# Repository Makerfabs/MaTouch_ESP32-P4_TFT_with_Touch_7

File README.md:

If you encounter the following error when compiling under Windows, please try enabling Windows long path support.
```txt
\MaTouch_ESP32-P4_TFT_with_Touch_7\examples\esp_brookesia_phone\managed_components\espressif__esp_wifi_remote\dummy_src.c.obj.d: No such file or directory
```

do :

```cmd
# Open PowerShell with administrator privileges
reg add "HKLM\SYSTEM\CurrentControlSet\Control\FileSystem" /v LongPathsEnabled /t REG_DWORD /d 1
```

Restart the system.

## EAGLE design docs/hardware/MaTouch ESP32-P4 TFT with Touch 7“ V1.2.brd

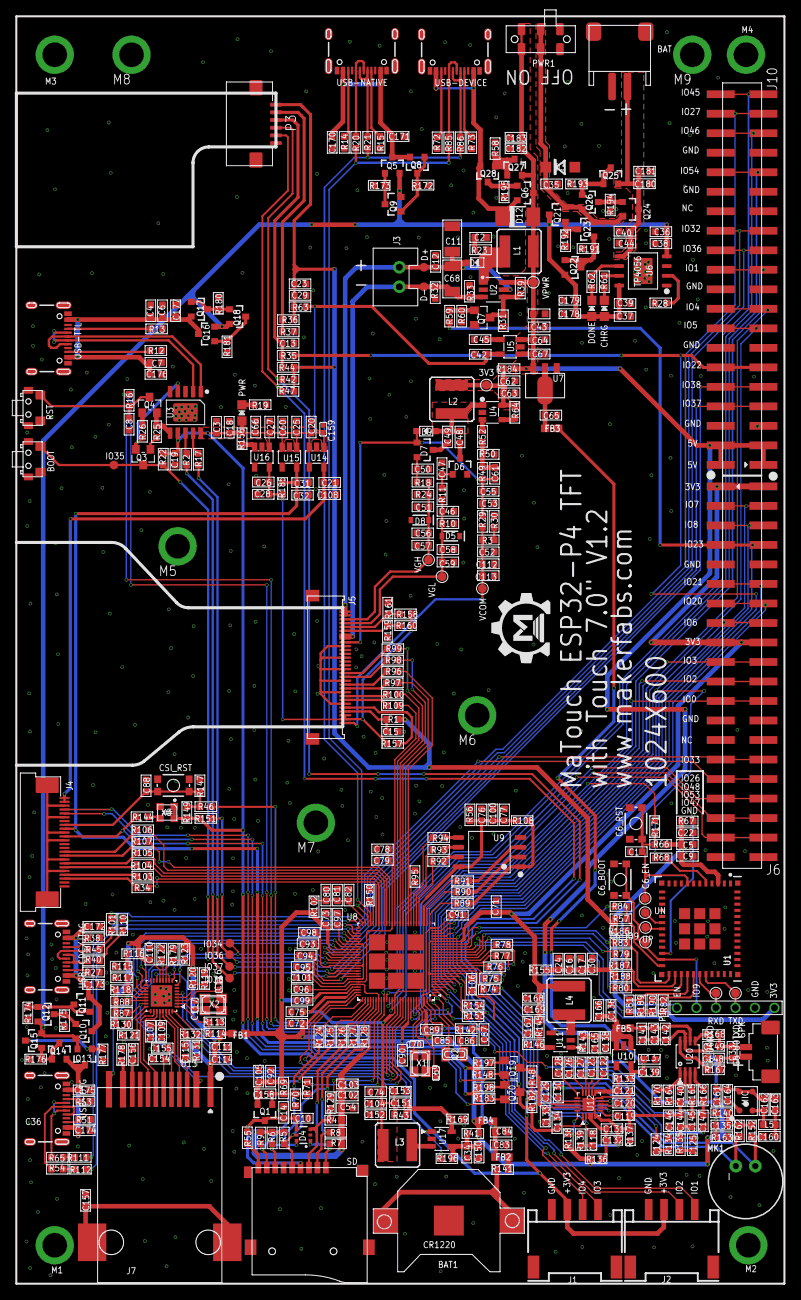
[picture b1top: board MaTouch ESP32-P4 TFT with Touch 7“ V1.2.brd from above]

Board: 2 copper layers, 100.0 x 165.0 mm, 507 parts (0 on the bottom side), 301 nets.

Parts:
3V3: TP_4545
BAT: JST-2P; HW2-SMD-2.0-90D
BAT1: CR1220-SMD
BOOT: TS24CA; 2*4*3.5MM
C1, C93, C94, C95, C96, C121, C124, C125, C126, C127, C128, C129, C130, C135, C140, C141: 1uF/16V; C0603
C2: 10pF/50V; DISCRETE_C0603
C3, C4, C6, C10, C16, C23, C29, C54, C63, C113: 10uF; DISCRETE_C0603
C5, C21, C22, C28, C31, C34, C35, C36, C38, C40, C42, C43, C65, C71, C74, C76, C78, C80, C83, C89, C97, C102, C107, C110, C114, C137, C142, C152, C160, C161, C165, C168, C170, C172, C174, C176, C178, C180, C182: 10uF; C0603
C6_BOOT, C6_RST: MOMENTARY-SWITCH-SPST-SMD-4.6X2.8MM; TACTILE_SWITCH_SMD_4.6X2.8MM
C6_EN, C6_IO9, C6_U0RXD, C6_U0TXD: TP_4545
C7, C8, C14, C17, C18, C19, C24, C26, C30, C32, C46, C47, C48, C49, C50, C51, C52, C53, C55, C60, C62, C66, C108, C112, C158: 0.1uF; DISCRETE_C0603
C9, C37, C39, C44, C67, C72, C73, C75, C77, C79, C81, C84, C90, C91, C92, C98, C99, C100, C103, C104, C105, C106, C109, C111, C115, C131, C132, C138, C139, C143, C145, C147, C150, C153, C154, C155, C166, C169, C171, C173, C175, C177, C179, C181, C183: 0.1uF; C0603
C11: 4.7uF/35V; DISCRETE_C1206
C12: 0.1uF/50V; DISCRETE_C0603
C13: NC; DISCRETE_C0603
C15: 100nF; DISCRETE_C0603
C20, C25, C27, C41, C64, C136: 4.7uF/16V; C0603
C33, C148, C149: 330pF/50V; C0603
C45: NC; C0603
C56, C57, C58, C59: 1uF; DISCRETE_C0603
C61: 10pF/25V; DISCRETE_C0603
C68: NC; DISCRETE_C1206
C69, C70, C116, C117: 12pF; DISCRETE_C0402
C82: 10nF; C0603
C85, C86: 20pF; DISCRETE_C0603
C87, C88: 15pF; DISCRETE_C0603
C101: 1uF; C0603
C118, C119, C120, C122, C123, C133, C134, C144, C146, C151, C167: 22pF; C0603
C156, C157: 1nF/50V; C0603
C159: 100nF; C0402
C162, C163: 33pF; C0603
C164: 100nF; C0603
CHRG: CHRG; CHIPLED_0805_NOOUTLINE
CSI_RST: MOMENTARY-SWITCH-SPST-SMD-4.6X2.8MM; TACTILE_SWITCH_SMD_4.6X2.8MM
D1, D9: 1N4148WS; SOD323
D3: W8/5.1V; SOD123
D4: SMF05C; SOT363
D5: 7.5V; SOD-323
D6, D7: 200mA/70V; SOT23-3
D8: 20V; SOD-323
D12: SS54; DO-214AC
D+: TP-D45MIL
D-: TP-D45MIL
DONE: GREEN; CHIPLED_0805_NOOUTLINE
FB1, FB2, FB3, FB4, FB5: 0603
IO34, IO35, IO36, IO37, IO38: TP-D45MIL
J1, J2: HW4-SMD-2.0-90D
J3: XH2.54-2P
J4: SMD26-50P-1760L450W
J5: 30P-0.5-90D-18.4X5.0
J6, J10: SMD2X20-254P-5080L750W920H
J7: HR961160C
L1, L2: 10µH/±30%; CR54
L3, L4: 2.2µH/±30%/3.4A; CR54
L5: BLM18BD252SN1; L0603
M1, M2, M3, M4, M5, M6, M7, M8, M9: M2.5
MIC: SAO-3729-M-42-008; MIC4-SMD-3.76X2.95MM
MK1: MIC-PTH; MICROPHONE-PTH-9.7MM
P1: DEBUG6; DEBUG*6
P3: 1X6P-1MM; 1*6P-SMT1MM
PWR: GREEN; CHIPLED_0805_NOOUTLINE
PWR1: JS102011JAQN; SMD-6-2.5MM
Q1, Q5, Q6, Q10, Q13, Q16, Q21, Q24: MOSFET-PCHANNEL; SOT23-3
Q2: 32.768K; XTAL3215
Q3, Q4, Q7: S8050; SOT23
Q8, Q9, Q11, Q12, Q14, Q15, Q17, Q18, Q22, Q23, Q25, Q26, Q27, Q28: 600mA/40V; SOT23-3
Q19, Q20: BS138; SOT23
R1, R39, R44, R58, R60, R64, R69, R70, R108, R156, R157, R158, R159, R172, R174, R176, R180, R191, R193: 10K; DISCRETE_R0603
R2, R17, R35, R41, R56, R63, R68, R74, R75, R76, R77, R78, R79, R80, R81, R82, R83, R84, R89, R90, R91, R92, R93, R94, R96, R97, R98, R99, R100, R102, R109, R124, R125, R126, R127, R128, R129, R133, R134, R135, R136, R137, R144, R147, R153, R154, R155, R163, R167, R168, R170, R171, R184, R185: 0R; R0603
R3: 0R; DISCRETE_R0603
R4, R6, R7, R8, R9, R10, R24, R55, R57, R173, R175, R177, R181, R186, R187, R188, R189, R190, R192, R194, R195: 51K; DISCRETE_R0603
R5, R31, R36, R37, R42, R47, R149, R160, R161: NC; DISCRETE_R0603
R11, R18: 220R; DISCRETE_R0603
R12, R13, R14, R15, R27, R38, R51, R53, R72, R73: 5.1K; DISCRETE_R0603
R16, R22, R25, R26, R66, R139, R143, R151, R164: 10K; R0603
R19: 1.2K; DISCRETE_R0603
R20, R21, R40, R45, R54, R65, R71, R85, R86, R101, R110, R111, R112: 33R; R0603
R23: 50R; DISCRETE_R0603
R28, R61, R62: 1.2K; R0603
R29: 2K; DISCRETE_R0603
R30: 1K; DISCRETE_R0603
R32, R33: 3.6R; DISCRETE_R0603
R34, R103, R104, R105, R106, R107: 100R; R0603
R43, R169: 499K/NC; R0603
R46, R196: NC; R0603
R48, R182: 3.3K; R0603
R49: 22K; DISCRETE_R0603
R50: 3.3K; DISCRETE_R0603
R52: 0K; DISCRETE_R0603
R59: 4.7K; DISCRETE_R0603
R67, R145: 100K; R0603
R87, R178, R179: 1.5K; R0603
R88: 1.5K/NC; R0603
R95, R150: 4.02K; R0603
R113, R116, R118, R120, R122, R123: 5.1K; R0603
R114, R115, R117, R119, R130: NC/5.1K; R0603
R121: 6.19K; R0603
R131, R132: NC/10K; R0603
R138: 10K/NC; R0603
R140: 200R; R0603
R141: 10R; R0603
R142: 0R/NC; R0603
R146: 22.1K; R0603
R148, R152, R162, R183, R197, R198: 2.2K; R0603
R165, R166: 150K; R0603
RST: TS24CA; 2*4*3.5MM
SD: 9P-SMD-W/-RING
SPK: 1X2P; 1X2P-SMT1.25MM
U1: ESP32-C6-MINI-1
U2: RY3730; SOT23-6
U3: CH340K; ESOP-10-EP-150MIL
U4: SGM6601YTN5G/TR; SOT-23-5
U5, U10, U14, U15, U16: SPX3819; SOT23-5
U6: TP4056; SOP8-1.27P
U7: AMS1117-3.3V; SOT89
U8: ESP32-P4; QFN105-35P-500L500W
U9: W25Q128JV; SOIC-8-208MIL
U11, U17: TLV62569DBVR; SOT23-5-95P-300L300W
U12: ES8311; QFN20-40P-300L300W55H
U13: IP101GRI; QFN32-40P-400W400L
U20: NS4150B; MSOP8-65P-490L300W110H
U$1: MAKERFABS_0.3
UN: TP_4545
UP: TP_4545
USB-CDC/JTAG: USB-C-16P-5
USB-DEVICE: USB-C-16P-5
USB-NATIVE: USB-C-16P-5
USB-OTG: USB-C-16P-5
USB-TTL: USB-C-16P-5
VCOM: TP_4545
VGH: TP_4545
VGL: TP_4545
VPWR: TP_4545
X1: 40MHz(10ppm); NX3225
X2: 25MHz(10ppm); NX3225
X3: 24MHz; OSC4-SMD-2.5X2.0X0.8MM

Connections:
3.3V: C5.1, C9.1, C16.2, C17.2, C22.1, C23.2, C24.2, C29.2, C30.2, P1.1, P3.1, R1.2, R36.2, R42.2, R44.2, R47.2, R57.2, R63.2, R66.2, R67.2, R155.1, R186.2, R187.2, R188.2, R189.2, R190.2, U1.3
25M_XI: C117.2, U13.2, X2.3
25M_XO: C116.1, U13.3, X2.1
+3V3: C3.2, C18.2, C19.2, C20.1, C25.1, C27.1, C42.1, C60.2, C66.2, C159.2, J1.3, J2.3, PWR.A, R22.2, R48.2, R63.1, R149.2, R151.2, R156.2, R182.2, U3.7, U3.10, U5.5, U14.1, U14.3, U15.1, U15.3, U16.1, X3.1, X3.4
A3V3: C137.1, C139.2, FB3.2, R133.2, U10.5
ADCVREF: C126.2, R140.1, U12.15
AGND: C118.2, C119.2, C120.2, C121.2, C126.1, C127.1, C128.2, C131.2, C132.2, C135.2, C140.2, C141.2, C142.2, C143.2, C144.2, C146.2, C148.2, C149.1, C161.1, C162.2, C163.2, C164.2, MIC.2, MIC.3, R137.1, R139.2, R163.1, R164.1, U12.5, U12.10, U12.21, U20.7
AVDD: C121.1, R133.1, U12.11
BAT: FB2.1, R141.1
C6_EN: C1.1, C6_EN.T, C6_RST.3, C6_RST.4, P1.6, R66.1, R171.2, U1.8
C6_IO2: R68.1, U1.5
C6_U0RXD: C6_U0RXD.T, P1.4, U1.30
C6_U0TXD: C6_U0TXD.T, P1.3, U1.31
CCLK: C87.2, J4.14, R142.1, R144.1
CODEC_CE: R138.2, R139.1, U12.20
COL: R119.2, R120.1, U13.4
CRS: R115.2, R116.1, U13.20
CSI_1V8: C31.1, C32.2, J4.16, R148.2, R183.2, R185.1, R197.2, R198.2, U15.5
CSI_2V8: C21.1, C108.2, J4.23, J4.24, U14.5
CSI_A_CLKN: J4.6, R104.2
CSI_A_CLKP: J4.7, R105.2
CSI_A_DATA0N: J4.9, R107.2
CSI_A_DATA0P: J4.10, R106.2
CSI_A_DATA1N: J4.3, R34.2
CSI_A_DATA1P: J4.4, R103.2
CSI_REXT: R150.1, U8.48
CSI_RST: C88.2, CSI_RST.3, CSI_RST.4, J4.17, R46.1, R147.2, R149.1
CSI_SCL: J4.21, Q20.2, R183.1
CSI_SDA: J4.20, Q19.2, R148.1
D+: U3.1, USB-TTL.A6, USB-TTL.B6
D-: U3.2, USB-TTL.A7, USB-TTL.B7
DACVREF: C127.2, U12.14
DSI_A_CLKN: J5.13, R98.1
DSI_A_CLKP: J5.14, R99.1
DSI_A_DATA0N: J5.7, R109.1
DSI_A_DATA0P: J5.8, R100.1
DSI_A_DATA1N: J5.10, R97.1
DSI_A_DATA1P: J5.11, R96.1
DSI_REXT: R95.1, U8.34
DTR: Q3.2, R26.2, U3.4
EN_DCDC: R196.1, U8.79, U17.1
ESP_EN: C8.2, Q4.3, R16.1, RST.2, U8.103
FB_DCDC: C151.2, R43.1, R169.2, U8.78, U17.5
FLASH_CK_A: R93.1, U9.6
FLASH_CS_A: R89.1, R108.2, U9.1
FLASH_D_A: R94.1, U9.5
FLASH_HD_A: R92.1, U9.7
FLASH_Q_A: R90.1, U9.2
FLASH_WP_A: R91.1, U9.3
GND: BAT.3, BAT.4, BAT.-, BAT1.-, BOOT.1, BOOT.3, BOOT.4, C1.2, C2.1, C3.1, C4.1, C5.2, C6.1, C6_BOOT.1, C6_BOOT.2, C6_RST.1, C6_RST.2, C7.1, C8.1, C9.2, C10.1, C11.1, C12.1, C13.1, C14.1, C15.1, C16.1, C17.1, C18.1, C19.1, C20.2, C21.2, C22.2, C23.1, C24.1, C25.2, C26.1, C27.2, C28.2, C29.1, C30.1, C31.2, C32.1, C34.2, C35.1, C36.1, C37.2, C38.2, C39.2, C40.2, C41.2, C42.2, C43.1, C44.2, C45.2, C46.1, C47.1, C50.1, C51.1, C52.1, C53.1, C54.1, C55.1, C56.1, C57.1, C58.1, C59.1, C60.1, C62.1, C63.1, C64.2, C65.2, C66.1, C67.1, C69.2, C70.1, C71.2, C72.2, C73.2, C74.2, C75.2, C76.2, C77.2, C78.2, C79.2, C80.2, C81.2, C82.2, C83.2, C84.2, C85.2, C86.2, C87.1, C88.1, C89.2, C90.2, C91.2, C92.2, C93.2, C94.2, C95.2, C96.2, C97.2, C98.2, C99.2, C100.2, C101.2, C102.2, C103.2, C104.2, C105.2, C106.2, C107.2, C108.1, C109.2, C110.2, C111.2, C112.1, C113.1, C114.2, C115.2, C116.2, C117.1, C122.2, C123.2, C133.2, C134.2, C136.2, C137.2, C138.1, C139.1, C150.1, C152.2, C153.1, C154.2, C155.2, C156.2, C157.2, C159.1, C165.2, C166.1, C168.2, C169.1, C170.2, C171.2, C172.2, C173.2, C174.2, C175.2, C176.2, C177.2, C178.2, C179.2, C180.2, C181.2, C182.2, C183.2, CSI_RST.1, CSI_RST.2, D3.A, D4.2, D5.C, D6.2, D8.A, J1.4, J1.SS1, J1.SS2, J2.4, J2.SS1, J2.SS2, J4.5, J4.8, J4.13, J4.15, J4.19, J4.22, J4.25, J4.26, J5.6, J5.9, J5.12, J5.15, J5.18, J5.21, J6.9, J6.10, J6.25, J6.26, J6.39, J6.40, J10.5, J10.6, J10.13, J10.14, J10.19, J10.20, J10.29, J10.30, J10.33, J10.34, M1.1, M2.1, M3.1, M4.1, M5.1, M6.1, M7.1, M8.1, M9.1, P1.2, P3.6, P3.7, P3.8, Q7.2, R10.1, R12.1, R13.1, R14.1, R15.1, R19.1, R24.1, R27.1, R28.2, R30.1, R31.1, R32.1, R33.1, R37.2, R38.1, R50.1, R51.1, R53.1, R58.1, R60.1, R70.1, R72.1, R73.1, R95.2, R113.1, R115.1, R117.1, R119.1, R121.1, R122.1, R131.1, R137.2, R146.1, R150.2, R159.1, R161.1, R169.1, R172.1, R173.1, R174.1, R175.1, R176.1, R177.1, R178.1, R180.1, R181.1, R191.1, R192.1, R193.1, R194.1, R195.1, RST.1, RST.3, RST.4, SD.6, SD.G1, SD.G2, SD.G3, SD.G4, SPK.3, SPK.4, U1.1, U1.2, U1.11, U1.14, U1.36, U1.37, U1.38, U1.39, U1.40, U1.41, U1.42, U1.43, U1.44, U1.45, U1.46, U1.47, U1.48, U1.49.1, U1.49.2, U1.49.3, U1.49.4, U1.49.5, U1.49.6, U1.49.7, U1.49.8, U1.49.9, U1.50, U1.51, U1.52, U1.53, U2.2, U3.3, U3.EP, U4.2, U5.2, U6.1, U6.3, U6.9, U7.1, U8.105, U8.106, U8.107, U8.108, U8.109, U8.110, U8.111, U8.112, U8.113, U9.4, U10.2, U11.2, U13.33, U14.2, U15.2, U16.2, U17.2, USB-CDC/JTAG.GND, USB-CDC/JTAG.GND2, USB-DEVICE.GND, USB-DEVICE.GND2, USB-NATIVE.GND, USB-NATIVE.GND2, USB-OTG.GND, USB-OTG.GND2, USB-TTL.GND, USB-TTL.GND2, X1.2, X1.4, X2.2, X2.4, X3.2
I2C_SCL: C134.1, P3.4, Q20.3, R42.1, R154.2, R182.1, U12.1
I2C_SDA: C133.1, P3.5, Q19.3, R47.1, R48.1, R153.2, U12.19
I2S_ASDOUT: R76.1, U12.7
I2S_DSDIN: R74.1, U12.9
I2S_LRCK: C120.1, R75.1, U12.8
I2S_MCLK: C118.1, R78.1, U12.2
I2S_SCLK: C119.1, R77.1, U12.6
IO0: C85.1, J6.23, J6.24, Q2.P$1, U8.104
IO1: C86.1, J10.21, J10.22, Q2.P$2, R142.2, U8.1
IO2: J6.21, J6.22, R46.2, U8.2
IO3: J1.1, J6.19, J6.20, U8.3
IO4: J1.2, J10.17, J10.18, U8.4
IO5: J10.15, J10.16, U8.5
IO6: J6.15, J6.16, R68.2, U8.6
IO7: J6.3, J6.4, R153.1, U8.7
IO8: J6.5, J6.6, R154.1, U8.8
IO9: R74.2, U8.10
IO9/BOOT: C6_BOOT.3, C6_BOOT.4, C6_IO9.T, P1.5, U1.23
IO10: R75.2, U8.11
IO11: R76.2, U8.12
IO12: R77.2, U8.13
IO12/USB_N: U1.17, UN.T
IO13: R78.2, U8.14
IO13/USB_P: U1.18, UP.T
IO14: R79.2, U8.15
IO15: R80.2, U8.16
IO16: R81.2, U8.17
IO17: R82.2, U8.18
IO18: R83.2, U8.19
IO19: R84.2, U8.20
IO20: J2.1, J6.13, J6.14, U8.22
IO21: J2.2, J6.11, J6.12, U8.23
IO22: J10.11, J10.12, R35.1, U8.24
IO23: J6.7, J6.8, R59.2, U8.25
IO24: R101.1, U8.52
IO25: R110.1, U8.53
IO26: J6.31, J6.32, R111.1, U8.55
IO27: J10.37, J10.38, R112.1, U8.56
IO28: U8.57, U13.19
IO29: U8.58, U13.18
IO30: U8.60, U13.17
IO31: R88.1, U8.61, U13.22
IO32: J10.25, J10.26, U8.63
IO33: J6.29, J6.30, U8.64
IO34: IO34.T, U8.65, U13.9
IO35: BOOT.2, IO35.T, Q3.3, R22.1, U8.66, U13.8
IO36: IO36.T, J10.23, J10.24, R151.1, U8.68
IO37: IO37.T, J10.7, J10.8, R17.1, U8.69
IO38: IO38.T, J10.9, J10.10, R2.1, U8.70
IO45: J10.39, J10.40, R71.1, U8.87
IO46: J10.35, J10.36, U8.88
IO47: J6.37, J6.38, U8.89
IO48: J6.33, J6.34, U8.90
IO49: U8.92, U13.5
IO50: U8.93, U13.10, U13.14
IO51: R131.2, R132.1, U8.94, U13.32
IO52: R87.1, U8.95, U13.23
IO53: J6.35, J6.36, R170.1, U8.97
IO54: J10.31, J10.32, R171.1, U8.98
LCD_AVDD: C53.2, C55.2, C61.2, D7.1, D9.-, J5.22, R29.2, R49.2
LCD_RST: C15.2, J5.4, R1.1
LCD_VCOM: C52.2, C112.2, C113.2, J5.1, R3.2, R29.1, VCOM.T
LCD_VDD: C26.2, C28.1, J5.2, J5.3, R157.2, R158.2, R160.2, R185.2, U16.5
LCD_VGH: C51.2, C56.2, C57.2, D8.C, J5.28, R18.1, R24.2, VGH.T
LCD_VGL: C46.2, C58.2, C59.2, D5.A, J5.27, R10.2, R11.2, VGL.T
LED+: C11.2, C12.2, C68.2, D1.-, D+.T, J3.1, J5.29, J5.30, U2.5
LED-: C68.1, D-.T, J3.2, J5.23, J5.24, R32.2, R33.2, U2.3
MICN: C130.2, MK1.2, R162.1, R163.2
MICP: C129.2, C160.2, MK1.1, R152.1
MKF_3V1: C107.1, C109.1, U13.28
MKF_3V3: C71.1, C72.1, C73.1, C89.1, C90.1, C92.1, C99.1, C105.1, C106.1, C158.2, C161.2, C164.1, C167.1, C168.1, C169.2, FB1.2, FB4.1, J6.1, J6.2, J6.17, J6.18, L4.P$2, MIC.1, Q1.2, R41.1, R69.2, R102.1, R136.1, R138.1, R145.2, R155.2, U8.9, U8.21, U8.62, U8.75, U8.77, U8.96, U8.101
MKF_LDO_VO1: C93.1, R56.1, U8.71
MKF_LDO_VO2: C94.1, C97.1, C98.1, U8.59, U8.67, U8.72
MKF_LDO_VO3: C78.1, C79.1, C95.1, C101.1, U8.41, U8.73
MKF_LDO_VO4: C54.2, C96.1, C102.1, C103.1, R4.2, R5.2, R6.2, R7.2, R8.2, R9.2, U8.74, U8.85
MKF_VBAT: C83.1, C84.1, FB2.2, FB4.2, R16.2, U8.102
MKF_VDD_HP: C74.1, C75.1, C91.1, C104.1, C151.1, C152.1, C153.2, L3.P$2, R43.2, U8.26, U8.76, U8.91
unnamed: C47.2, D6.1, R11.1
unnamed: Q4.1, R26.1
unnamed: Q3.1, R25.1
unnamed: C61.1, R49.1, R50.2, R52.1
unnamed: R38.2, USB-CDC/JTAG.A5
unnamed: R15.2, USB-NATIVE.A5
unnamed: PWR.C, R19.2
unnamed: C48.2, D6.3
unnamed: C48.1, C49.2, D9.+, L2.P$2, U4.1
unnamed: R13.2, USB-TTL.A5
unnamed: R12.2, USB-TTL.B5
unnamed: C49.1, D7.3
unnamed: C50.2, D7.2, R18.2
unnamed: R14.2, USB-NATIVE.B5
unnamed: R52.2, U4.3
unnamed: R3.1, R30.2
unnamed: D1.+, L1.P$2, R23.2, U2.1
unnamed: R27.2, USB-CDC/JTAG.B5
unnamed: R64.1, U4.4
unnamed: R53.2, USB-OTG.A5
unnamed: C34.1, C150.2, R41.2, R196.2, U17.4
unnamed: C2.2, R23.1
unnamed: L3.P$1, U17.3
unnamed: Q7.3, R31.2, R39.1, U2.4
unnamed: R51.2, USB-OTG.B5
unnamed: Q22.1, Q22.3, Q23.1, R191.2
unnamed: Q21.1, Q23.3, R192.2
unnamed: R67.1, U1.22
unnamed: Q7.1, R59.1, R60.2
unnamed: R28.1, U6.2
unnamed: R61.2, U6.7
unnamed: R62.2, U6.6
unnamed: CHRG.C, R61.1
unnamed: DONE.C, R62.1
unnamed: R73.2, USB-DEVICE.A5
unnamed: C158.1, Q1.1, R69.1, R70.2, R71.2
unnamed: R72.2, USB-DEVICE.B5
unnamed: R144.2, X3.3
unnamed: R156.1, U16.3
unnamed: BAT1.+$1, BAT1.+$2, R141.2
unnamed: C160.1, C163.1, L5.2
unnamed: C130.1, U12.17
unnamed: C162.1, L5.1, MIC.4
unnamed: C167.2, R145.1, R146.2, U11.5
unnamed: C122.1, C125.1, U12.12
unnamed: R17.2, U3.9
unnamed: C123.1, C124.1, U12.13
unnamed: C124.2, R134.1
unnamed: R2.2, U3.8
unnamed: C125.2, R135.1
unnamed: C129.1, U12.18
unnamed: C131.1, C132.1, R136.2, U12.3, U12.4
unnamed: C135.1, R140.2, R152.2, R162.2
unnamed: C140.1, U20.2
unnamed: C141.1, C142.1, C143.1, FB5.1, U20.6
unnamed: C145.2, R165.1
unnamed: C147.2, R166.1
unnamed: C33.2, C149.2, R168.2, SPK.2
unnamed: C33.1, C148.1, R167.2, SPK.1
unnamed: R143.1, U11.1
unnamed: Q11.1, Q11.3, Q12.1, R174.2
unnamed: L4.P$1, U11.3
unnamed: R89.2, U8.27
unnamed: R90.2, U8.28
unnamed: R91.2, U8.29
unnamed: Q8.1, Q8.3, Q9.1, R172.2
unnamed: R92.2, U8.31
unnamed: R93.2, U8.32
unnamed: R94.2, U8.33
unnamed: C154.1, J7.6
unnamed: R96.2, U8.35
unnamed: R97.2, U8.36
unnamed: R98.2, U8.37
unnamed: R99.2, U8.38
unnamed: R100.2, U8.39
unnamed: C45.1, U5.4
unnamed: C155.1, J7.5
unnamed: C80.1, C81.1, C82.1, R102.2, U8.51
unnamed: C156.1, J7.10
unnamed: C157.1, J7.13, J7.14
unnamed: J7.11, R178.2
unnamed: R103.1, U8.47
unnamed: R34.1, U8.46
unnamed: R104.1, U8.45
unnamed: R105.1, U8.44
unnamed: R106.1, U8.43
unnamed: R107.1, U8.42
unnamed: R109.2, U8.40
unnamed: J7.2, R179.1
unnamed: Q5.1, Q9.3, R173.2
unnamed: Q10.1, Q12.3, R175.2
unnamed: Q14.1, Q14.3, Q15.1, R176.2
unnamed: Q13.1, Q15.3, R177.2
unnamed: Q17.1, Q17.3, Q18.1, R180.2
unnamed: Q16.1, Q18.3, R181.2
unnamed: 3V3.T, C62.2, C63.2, L2.P$1, R64.2, R184.2, U4.5
unnamed: Q25.1, Q25.3, Q26.1, R193.2
unnamed: Q24.1, Q26.3, R194.2
unnamed: Q6.1, Q28.3, R195.2
unnamed: Q20.1, R198.1
unnamed: R124.1, U8.80
unnamed: R125.1, U8.81
unnamed: R126.1, U8.82
unnamed: R127.1, U8.83
unnamed: R128.1, U8.84
unnamed: Q19.1, R197.1
unnamed: R129.1, U8.86
unnamed: Q27.1, Q27.3, Q28.1, R58.2
OUTN: C146.1, C147.1, R134.2
OUTP: C144.1, C145.1, R135.2
PA_CTRL: R164.2, R170.2, U20.1
PA_INL+: R165.2, U20.3
PA_INL-: R166.2, U20.4
PA_OUTL+: R167.1, U20.8
PA_OUTL-: R168.1, U20.5
PHY_3V3: C110.1, C111.1, C114.1, C115.1, FB1.1, J7.1, R87.2, R88.2, R114.2, R116.2, R118.2, R120.2, R123.2, R130.2, R132.2, U13.13, U13.31
PHY_AD0: R123.1, R179.2, U13.11
PHY_AD3: J7.12, R122.2, U13.12
PHY_ISET: R121.2, U13.25
PHY_TESTON: R130.1, U13.24
RD+: J7.7, U13.27
RD-: J7.8, U13.26
RTS: Q4.2, R25.2, U3.6
RXER: R117.2, R118.1, U13.21
SD1_CLK: D4.5, R5.1, R128.2, SD.5
SD1_CMD: D4.3, R4.1, R129.2, SD.3
SD1_D0: D4.6, R6.1, R124.2, SD.7
SD1_D1: R9.1, R125.2, SD.8
SD1_D2: D4.1, R7.1, R126.2, SD.1
SD1_D3: R8.1, R127.2, SD.2
SD1_VDD: C10.2, C14.2, D4.4, Q1.3, R55.1, SD.4
SD2_CLK: R83.1, R186.1, U1.25
SD2_CMD: R57.1, R84.1, U1.24
SD2_D0: R79.1, R187.1, U1.26
SD2_D1: R80.1, R188.1, U1.27
SD2_D2: R81.1, R189.1, U1.28
SD2_D3: R82.1, R190.1, U1.29
SD_DET: R55.2, SD.9
SHLR: J5.25, R159.2, R160.1
STBYB: J5.5, R157.1
TD+: J7.3, U13.30
TD-: J7.4, U13.29
TP_INT: P3.2, R36.1, R37.1
TP_RST: C13.2, P3.3, R35.2, R44.1
TXER: R113.2, R114.1, U13.1
UPDN: J5.26, R158.1, R161.2
USB1P1_N: R45.2, R101.2
USB1P1_N_2: R65.2, R111.2
USB1P1_P: R40.2, R110.2
USB1P1_P_2: R54.2, R112.2
USB1_5V: C170.1, C171.1, Q5.3, Q8.2, USB-NATIVE.VBUS1, USB-NATIVE.VBUS2
USB1_D+: R20.1, USB-NATIVE.A6, USB-NATIVE.B6
USB1_D-: R21.1, USB-NATIVE.A7, USB-NATIVE.B7
USB2_5V: C172.1, C173.1, Q10.3, Q11.2, USB-CDC/JTAG.VBUS1, USB-CDC/JTAG.VBUS2
USB2_D+: R40.1, USB-CDC/JTAG.A6, USB-CDC/JTAG.B6
USB2_D-: R45.1, USB-CDC/JTAG.A7, USB-CDC/JTAG.B7
USB3_5V: C174.1, C175.1, Q13.3, Q14.2, USB-OTG.VBUS1, USB-OTG.VBUS2
USB3_D+: R54.1, USB-OTG.A6, USB-OTG.B6
USB3_D-: R65.1, USB-OTG.A7, USB-OTG.B7
USB4_5V: D12.C, Q6.2, Q28.2, USB-DEVICE.VBUS1, USB-DEVICE.VBUS2
USB4_D+: R85.1, USB-DEVICE.A6, USB-DEVICE.B6
USB4_D-: R86.1, USB-DEVICE.A7, USB-DEVICE.B7
USB_5V: C36.2, C37.1, C38.1, C39.1, C178.1, C179.1, CHRG.A, DONE.A, Q5.2, Q9.2, Q10.2, Q12.2, Q13.2, Q15.2, Q16.2, Q18.2, Q21.3, Q22.2, U6.4, U6.8
USB_DM: R21.2, R86.2, U8.49
USB_DP: R20.2, R85.2, U8.50
VBAT: BAT.+, C40.1, C44.1, C180.1, C181.1, Q24.3, Q25.2, U6.5
VBUS: C4.2, C6.2, C7.2, C176.1, C177.1, Q16.3, Q17.2, USB-TTL.VBUS1, USB-TTL.VBUS2
VCC_5V: C41.1, C43.2, C64.1, C67.2, C136.1, C138.2, C165.1, C166.2, C182.1, C183.1, D12.A, FB5.2, J10.1, J10.2, J10.3, J10.4, L1.P$1, PWR1.3, PWR1.3@1, Q6.3, Q27.2, R39.2, R143.2, R184.1, U2.6, U5.1, U5.3, U7.3, U10.1, U10.3, U11.4, VPWR.T
VDD: C65.1, FB3.1, U7.2, U7.4
VDD_FLASH: C76.1, C77.1, C100.1, R56.2, R108.1, U8.30, U9.8
VMID: C128.1, U12.16
VPP: C35.2, D3.C, PWR1.2, PWR1.2@1, Q21.2, Q23.2, Q24.2, Q26.2
XTAL_N: C70.2, U8.99, X1.3
XTAL_P: C69.1, U8.100, X1.1

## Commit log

2025-09-25 add esp_brookesia_phone
2025-09-25 add README.md
2025-09-27 README.md
2025-09-28 add docs
2025-09-28 add hardware&datasheet

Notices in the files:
parts and their libraries:
microbuilder: This work is placed in the public domain, and may be freely used for commercial and non-commercial work with the following conditions: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
SparkFun-Coils: Licensing: Creative Commons ShareAlike 4.0 International - https://creativecommons.org/licenses/by-sa/4.0
